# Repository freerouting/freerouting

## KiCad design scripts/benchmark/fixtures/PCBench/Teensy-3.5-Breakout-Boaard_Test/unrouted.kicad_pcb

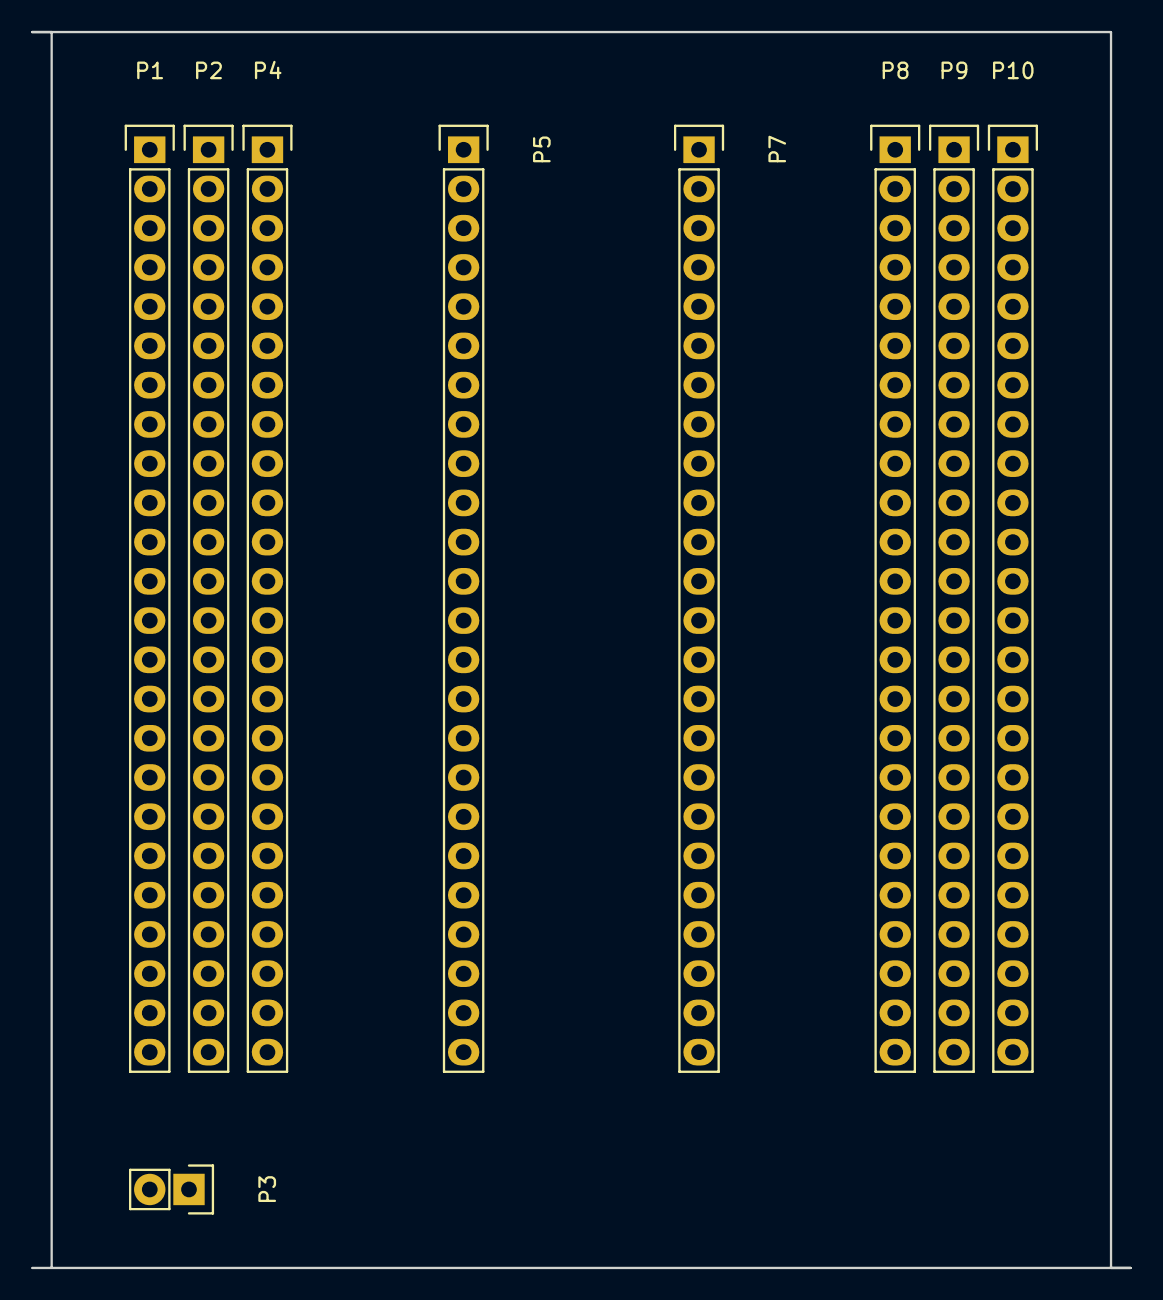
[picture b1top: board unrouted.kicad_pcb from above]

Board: 2 copper layers, 71.1 x 80.0 mm, 9 parts (0 on the bottom side), 52 nets, no tracks yet.

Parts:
P1, P2, P4, P8, P9, P10: CONN_01X24; Pin_Header_Straight_1x24
P3: CONN_01X02; Pin_Header_Straight_1x02
P5, P7: CONN_01X24; Socket_Strip_Straight_1x24

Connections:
unnamed: P1.1, P1.2, P1.3, P1.4, P1.5, P1.6, P1.7, P1.8, P1.9, P1.10, P1.11, P1.12, P1.13, P1.14, P1.15, P1.16, P1.17, P1.18, P1.19, P1.20, P1.21, P1.22, P1.23, P1.24
unnamed: P2.1, P2.2, P2.3, P2.4, P2.5, P2.6, P2.7, P2.8, P2.9, P2.10, P2.11, P2.12, P2.13, P2.14, P2.15, P2.16, P2.17, P2.18, P2.19, P2.20, P2.21, P2.22, P2.23, P2.24
unnamed: P4.1, P5.1
unnamed: P4.2, P5.2
unnamed: P4.3, P5.3
unnamed: P4.4, P5.4
unnamed: P4.5, P5.5
unnamed: P4.6, P5.6
unnamed: P4.7, P5.7
unnamed: P4.8, P5.8
unnamed: P4.9, P5.9
unnamed: P4.10, P5.10
unnamed: P4.11, P5.11
unnamed: P4.12, P5.12
unnamed: P4.13, P5.13
unnamed: P4.14, P5.14
unnamed: P4.15, P5.15
unnamed: P4.16, P5.16
unnamed: P4.17, P5.17
unnamed: P4.18, P5.18
unnamed: P4.19, P5.19
unnamed: P4.20, P5.20
unnamed: P4.21, P5.21
unnamed: P4.22, P5.22
unnamed: P4.23, P5.23
unnamed: P4.24, P5.24
unnamed: P7.1, P8.1
unnamed: P7.2, P8.2
unnamed: P7.3, P8.3
unnamed: P7.4, P8.4
unnamed: P7.5, P8.5
unnamed: P7.6, P8.6
unnamed: P7.7, P8.7
unnamed: P7.8, P8.8
unnamed: P7.9, P8.9
unnamed: P7.10, P8.10
unnamed: P7.11, P8.11
unnamed: P7.12, P8.12
unnamed: P7.13, P8.13
unnamed: P7.14, P8.14
unnamed: P7.15, P8.15
unnamed: P7.16, P8.16
unnamed: P7.17, P8.17
unnamed: P7.18, P8.18
unnamed: P7.19, P8.19
unnamed: P7.20, P8.20
unnamed: P7.21, P8.21
unnamed: P7.22, P8.22
unnamed: P7.23, P8.23
unnamed: P7.24, P8.24
unnamed: P9.1, P9.2, P9.3, P9.4, P9.5, P9.6, P9.7, P9.8, P9.9, P9.10, P9.11, P9.12, P9.13, P9.14, P9.15, P9.16, P9.17, P9.18, P9.19, P9.20, P9.21, P9.22, P9.23, P9.24
unnamed: P10.1, P10.2, P10.3, P10.4, P10.5, P10.6, P10.7, P10.8, P10.9, P10.10, P10.11, P10.12, P10.13, P10.14, P10.15, P10.16, P10.17, P10.18, P10.19, P10.20, P10.21, P10.22, P10.23, P10.24

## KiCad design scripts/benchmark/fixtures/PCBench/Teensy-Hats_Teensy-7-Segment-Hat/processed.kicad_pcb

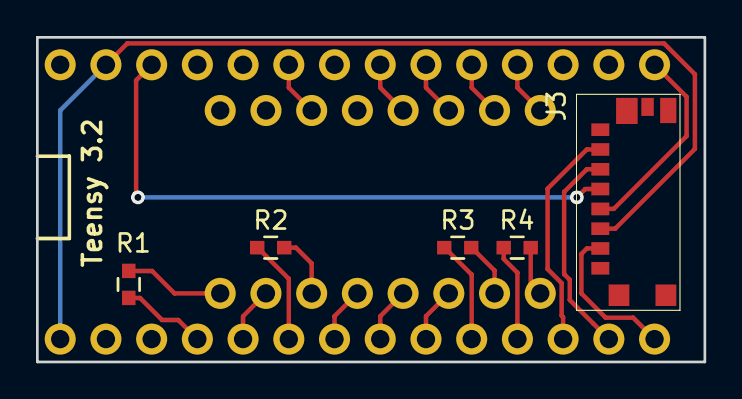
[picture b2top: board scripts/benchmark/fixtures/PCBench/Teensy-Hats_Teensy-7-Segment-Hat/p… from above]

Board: 2 copper layers, 37.1 x 18.0 mm, 7 parts (1 on the bottom side), 23 nets.

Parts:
J1: TEENSY3.2-72MHz-SIMPLE; TEENSY-3.2-SIMPLE
J3: MICRO-SD; CONN-SD-MICRO-MOLEX-0475710001
LED1: LED-4x7-SEGMENT-LTC-4727JR; DIP-16-W10.16MM-CIRCLEPADS
R1, R2, R3, R4: 470; RLC-0603-SMD

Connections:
+3V3: J1.3V2, J3.4
/A: J1.18, LED1.14
/B: J1.16, LED1.16
/C: J1.19, LED1.13
/D: J1.7, LED1.3
/DIGIT1: J1.9, R4.1
/DIGIT2: J1.8, R3.1
/DIGIT3: J1.4, R2.1
/DIGIT4: J1.2, R1.1
/DP: J1.3, LED1.7
/E: J1.5, LED1.5
/F: J1.21, LED1.11
/G: J1.17, LED1.15
/L: J1.6, LED1.4
/MISO: J1.12, J3.7
/MOSI: J1.11, J3.3
/SCLK: J1.13, J3.5
/SD_CS: J1.10, J3.2
GND: J1.AG, J1.G1, J3.6
unnamed: LED1.1, R4.2
unnamed: LED1.2, R3.2
unnamed: LED1.6, R2.2
unnamed: LED1.8, R1.2

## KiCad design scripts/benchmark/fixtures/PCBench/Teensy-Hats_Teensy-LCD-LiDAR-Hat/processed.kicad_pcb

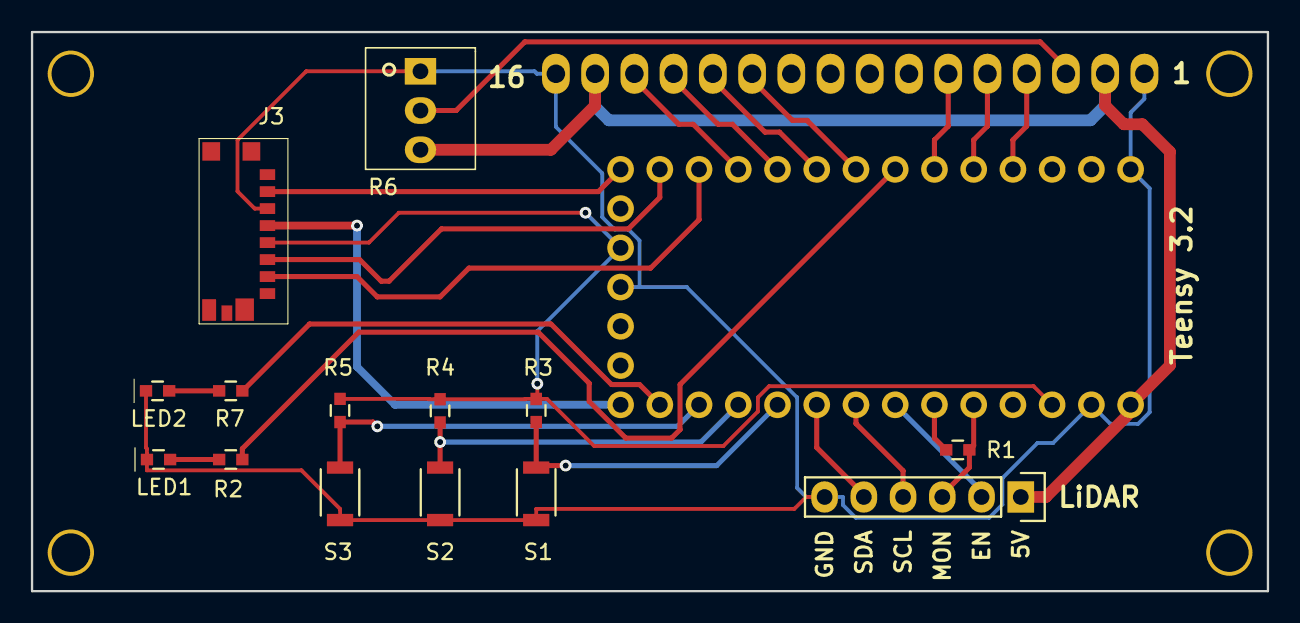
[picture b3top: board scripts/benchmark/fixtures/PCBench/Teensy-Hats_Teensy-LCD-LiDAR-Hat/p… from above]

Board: 2 copper layers, 80.0 x 36.2 mm, 16 parts (1 on the bottom side), 27 nets.

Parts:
J1: TEENSY3.2-72MHz; TEENSY-3.2-NOSILK
J2: LIDAR-LITE; CONN-HEADER-STRAIGHT-P2.54MM-1x06
J3: MICRO-SD; CONN-SD-MICRO-MOLEX-0475710001
LCD1: LCD-16x2; LCD-1602A
LED1, LED2: AMBER; LED-0603-SMD
R1, R2, R3, R4, R5, R7: 1K; RLC-0603-SMD
R6: 10K; RES-TRIMPOT-BOURNS-3362-SQUARE-TH-CENTER
S1: BUTTON1; SWITCH-OMRON-MOMENTARY-SMD-B3U-1000P
S2: BUTTON2; SWITCH-OMRON-MOMENTARY-SMD-B3U-1000P
S3: BUTTON3; SWITCH-OMRON-MOMENTARY-SMD-B3U-1000P

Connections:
+3V3: J1.3V1, J1.3V2, J3.4, R3.1, R4.1, R5.1
+5V: J1.VIN, J2.1, LCD1.2, LCD1.15, R6.3
/BUTTON1: J1.17, R3.2, S1.1
/BUTTON2: J1.16, R4.2, S2.1
/BUTTON3: J1.15, R5.2, S3.1
/LCD_D4: J1.6, LCD1.11
/LCD_D5: J1.7, LCD1.12
/LCD_D6: J1.8, LCD1.13
/LCD_D7: J1.9, LCD1.14
/LCD_EN: J1.4, LCD1.6
/LCD_RS: J1.2, LCD1.4
/LCD_RW: J1.3, LCD1.5
/LED1: J1.5, R2.1
/LED2: J1.14, R7.1
/LIDAR_EN: J1.20, J2.2
/LIDAR_MONITOR: J1.22, J2.3, R1.2
/LIDAR_TRIGGER: J1.21, R1.1
/MISO: J1.12, J3.7
/MOSI: J1.11, J3.3
/SCL: J1.19, J2.4
/SCLK: J1.13, J3.5
/SDA: J1.18, J2.5
/SD_CS: J1.10, J3.2
GND: J1.AG, J1.G1, J1.G2, J2.6, J3.6, LCD1.1, LCD1.16, LED1.1, LED2.1, R6.1, S1.2, S2.2, S3.2
unnamed: LCD1.3, R6.2
unnamed: LED1.2, R2.2
unnamed: LED2.2, R7.2

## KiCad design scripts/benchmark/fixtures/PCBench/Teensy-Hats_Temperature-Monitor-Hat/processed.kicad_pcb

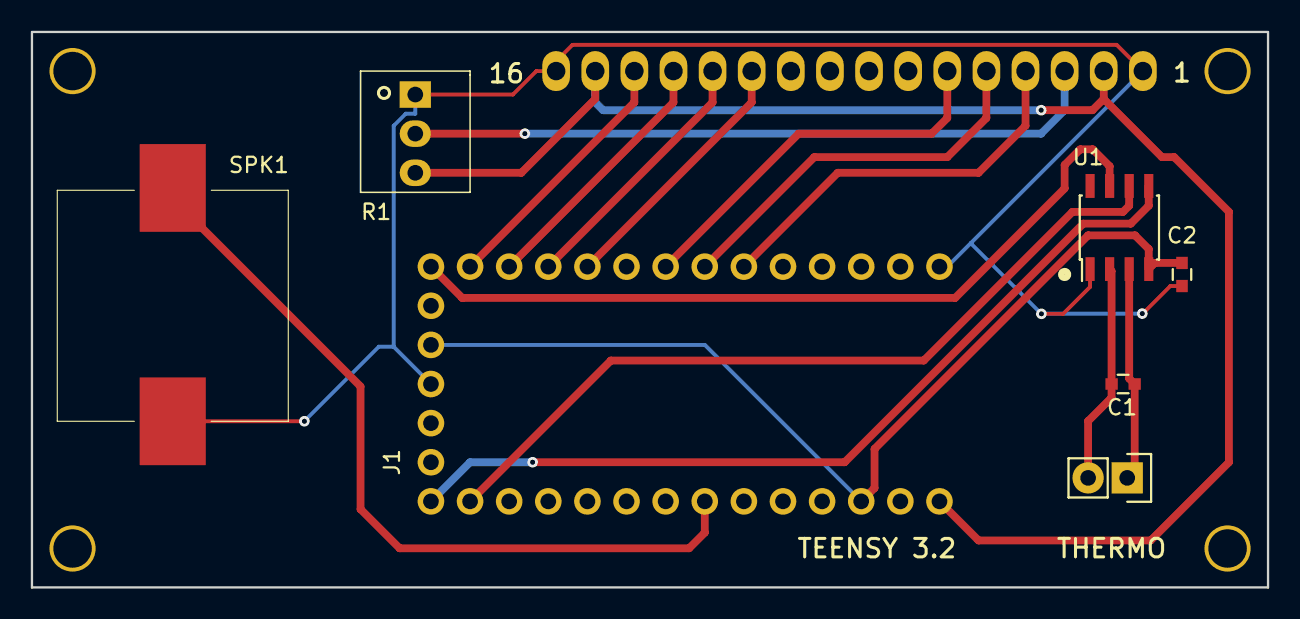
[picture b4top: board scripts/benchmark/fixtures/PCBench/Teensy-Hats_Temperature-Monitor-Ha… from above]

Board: 2 copper layers, 80.3 x 36.1 mm, 8 parts (1 on the bottom side), 17 nets.

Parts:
C1, C2: 100nF; RLC-0603-SMD
J1: TEENSY3.2-72MHz; TEENSY-3.2-NOSILK
J2: THERMO; CONN-ONSHORE-SCREW-GREEN-2PIN-TH
LCD1: LCD-MODULE-16X2-CHARACTER-1602A-CUSTOM1; LCD-1602A
R1: 10K; RES-TRIMPOT-BOURNS-3362-SQUARE-TH-CENTER
SPK1: BUZZER; SPEAKER-CMT-1603
U1: MAX31855; SOIC-8-3.9x4.9MM-P1.27MM

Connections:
+3V3: C2.1, J1.3V1, J1.3V2, U1.4
+5V: J1.VIN, LCD1.2, LCD1.15, R1.3
GND: C2.2, J1.G1, J1.G2, LCD1.1, LCD1.16, R1.1, SPK1.2, U1.1
unnamed: C1.1, J2.1, U1.3
unnamed: C1.2, J2.2, U1.2
unnamed: J1.4, LCD1.4
unnamed: J1.5, LCD1.5
unnamed: J1.6, LCD1.6
unnamed: J1.8, LCD1.11
unnamed: J1.9, LCD1.12
unnamed: J1.10, LCD1.13
unnamed: J1.11, LCD1.14
unnamed: J1.12, U1.7
unnamed: J1.13, U1.5
unnamed: J1.14, U1.6
unnamed: J1.20, SPK1.1
unnamed: LCD1.3, R1.2

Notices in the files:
scripts/benchmark/fixtures/PCBench/Teensy-Hats_Temperature-Monitor-Hat/processed.kicad_pcb:
Released under the CERN Open Hardware License v1.2
